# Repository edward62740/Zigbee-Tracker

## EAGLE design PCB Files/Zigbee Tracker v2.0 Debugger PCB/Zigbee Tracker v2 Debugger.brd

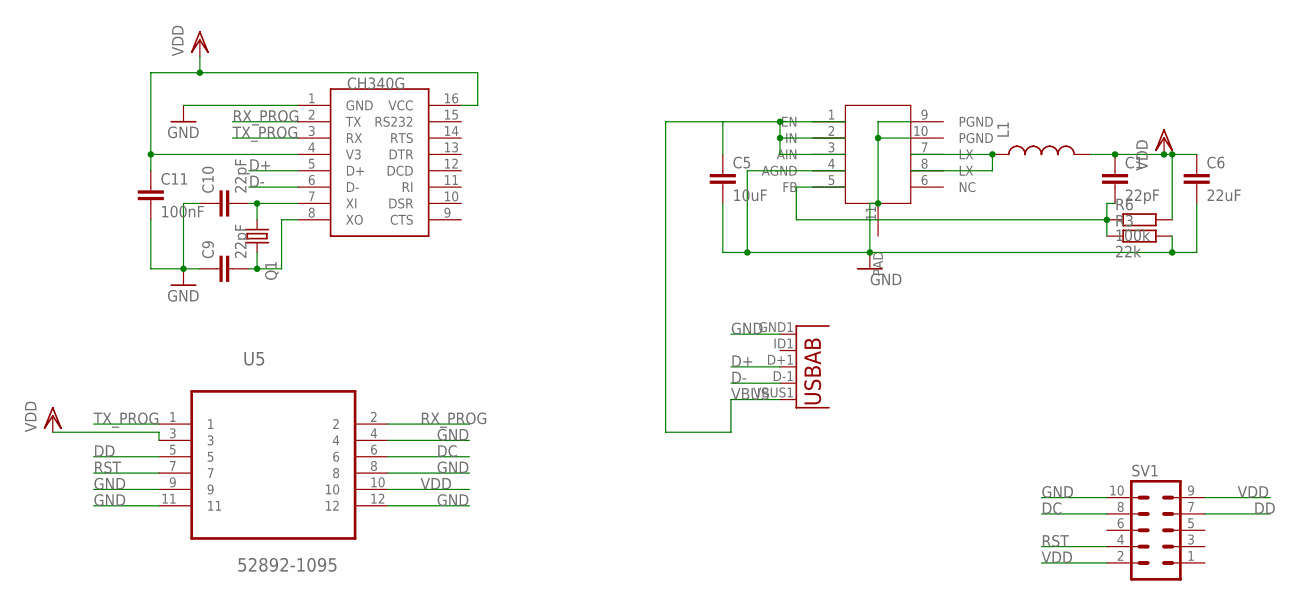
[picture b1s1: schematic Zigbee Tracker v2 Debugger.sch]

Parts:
C1, C9, C10: 22pF; C0402
C5: 10uF; C0402
C6: 22uF; C0402
C11: 100nF; C0402
L1: INDUCTOR; L0603
Q1: KX-7; 3.2X2.5_KX-7
R3: 22k; R0402
R6: 100k; R0402
SV1: MA05-2
U1: USB""; USB-MICRO-SMD
U5: 52892-1095; MOLEX_52892-1095
U$1: XM5152; SON50P300X300X80-11T170X240
U$2: CH340G; SOIC16

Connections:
D+: U1.D+1 (D+), U$2.5 (D+)
D-: U1.D-1 (D-), U$2.6 (D-)
DC: SV1.8, U5.6
DD: SV1.7, U5.5
GND: C5.2, C6.2, C9.1, C10.1, C11.2, R3.2, SV1.10, U1.GND1 (GND), U5.4, U5.8, U5.9, U5.11, U5.12, U$1.4 (AGND), U$1.9 (PGND), U$1.10 (PGND), U$1.11 (PAD), U$2.1 (GND)
unnamed: L1.1, U$1.7 (LX), U$1.8 (LX)
unnamed: C9.2, Q1.3 (2), U$2.8 (XO)
unnamed: C10.2, Q1.1, U$2.7 (XI)
unnamed: C1.2, R3.1, R6.1, U$1.5 (FB)
RST: SV1.4, U5.7
RX_PROG: U5.2, U$2.2 (TX)
TX_PROG: U5.1, U$2.3 (RX)
VBUS: C5.1, U1.VBUS1 (VBUS), U$1.1 (EN), U$1.2 (IN), U$1.3 (AIN)
VDD: C1.1, C6.1, C11.1, L1.2, R6.2, SV1.2, SV1.9, U5.3, U5.10, U$2.4 (V3), U$2.16 (VCC)

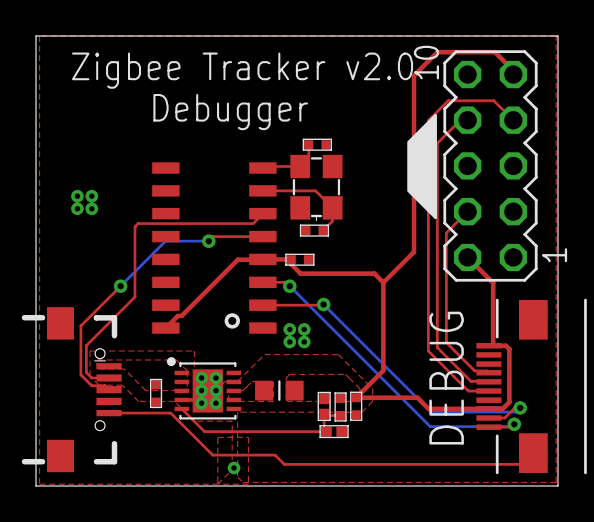
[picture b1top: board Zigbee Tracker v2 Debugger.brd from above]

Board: 2 copper layers, 29.0 x 25.0 mm, 15 parts (0 on the bottom side), 14 nets.

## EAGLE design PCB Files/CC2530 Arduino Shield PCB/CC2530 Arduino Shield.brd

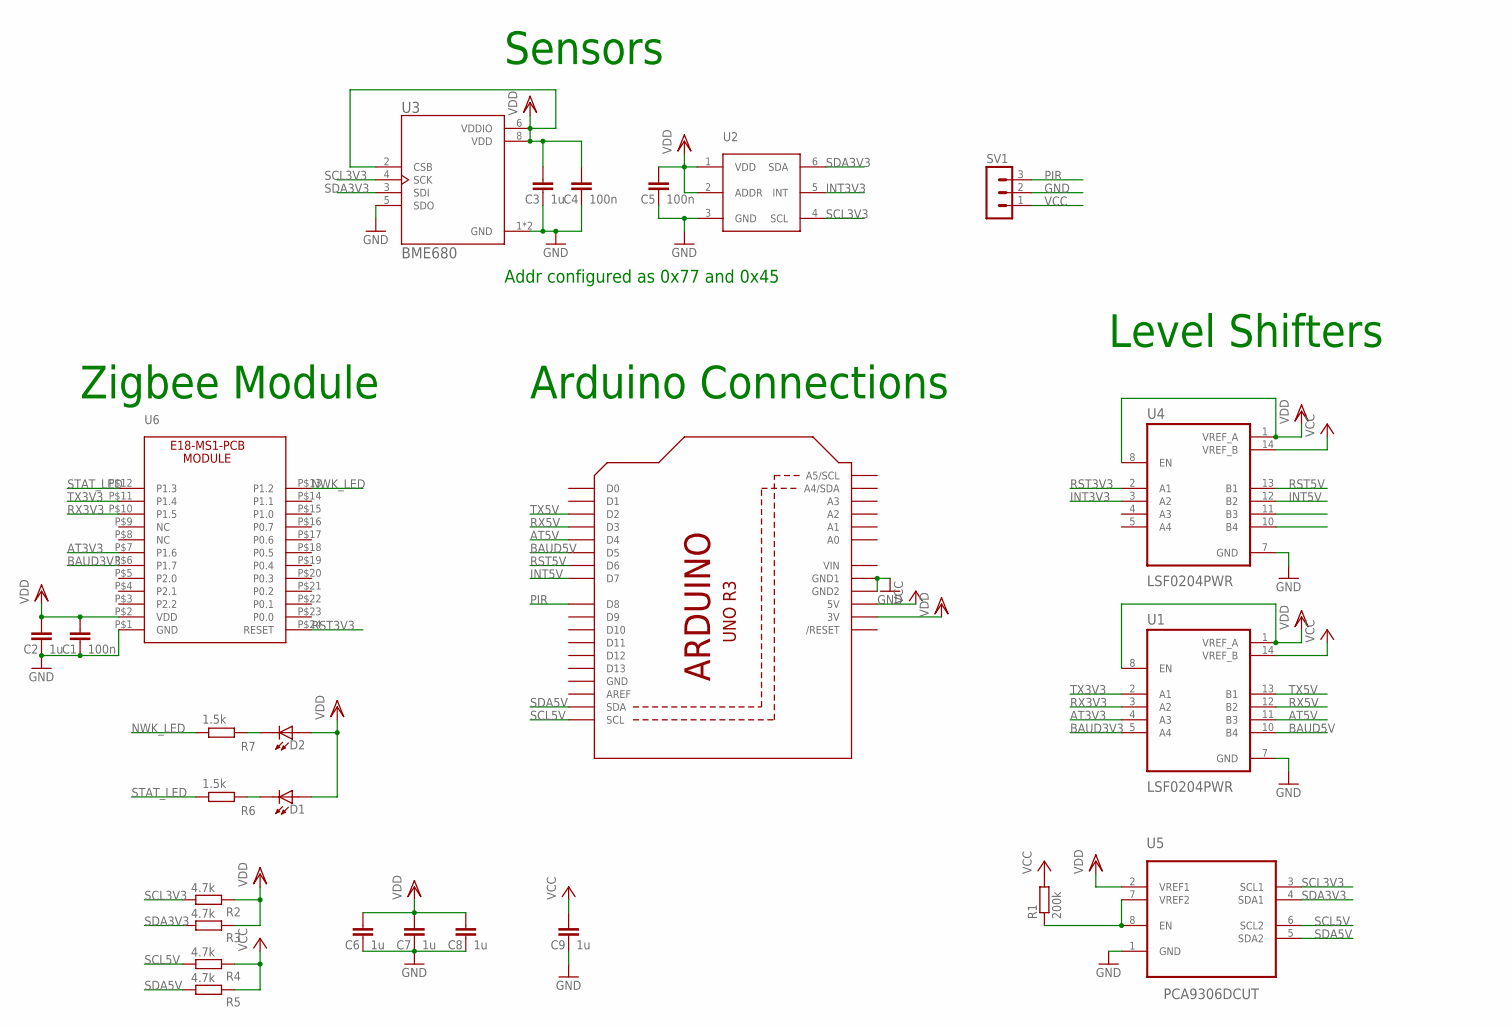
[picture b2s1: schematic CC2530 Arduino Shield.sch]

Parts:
C1, C4, C5: 100n; C0402
C2, C3, C6, C7, C8, C9: 1u; C0402
D1, D2: VLMG1500-GS08; LEDC1005X35N
Q1: ARDUINOR3-NOIOREF-NOTEXT; ARDUINOR3-NOTEXT-NOIOREF
R1: 200k; R0402
R2, R3, R4, R5: 4.7k; R0402
R6, R7: 1.5k; R0402
SV1: MA03-1
U1, U4: LSF0204PWR; SOP65P640X120-14N
U2: TI-OPT3001
U3: BME680; PSON80P300X300X100-8N
U5: PCA9306DCUT; SOP50P310X90-8N
U6: E18; E18-MS1-PCB

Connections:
AT3V3: U1.4 (A3), U6.P$7 (P1.6)
AT5V: Q1.D4, U1.11 (B3)
BAUD3V3: U1.5 (A4), U6.P$6 (P1.7)
BAUD5V: Q1.D5, U1.10 (B4)
GND: C1.2, C2.2, C3.2, C4.2, C5.2, C6.2, C7.2, C8.2, C9.2, Q1.GND, Q1.GND1, Q1.GND2, SV1.2, U1.7 (GND), U2.3 (GND), U3.1 (GND), U3.5 (SDO), U3.7 (GND), U4.7 (GND), U5.1 (GND), U6.P$1 (GND)
INT3V3: U2.5 (INT), U4.3 (A2)
INT5V: Q1.D7, U4.12 (B2)
unnamed: R1.1, U5.7 (VREF2), U5.8 (EN)
unnamed: D2.2, R7.2
unnamed: D1.2, R6.2
NWK_LED: R7.1, U6.P$13 (P1.2)
PIR: Q1.D8, SV1.3
RST3V3: U4.2 (A1), U6.P$24 (RESET)
RST5V: Q1.D6, U4.13 (B1)
RX3V3: U1.3 (A2), U6.P$10 (P1.5)
RX5V: Q1.D3, U1.12 (B2)
SCL3V3: R2.2, U2.4 (SCL), U3.4 (SCK), U5.3 (SCL1)
SCL5V: Q1.SCL, R4.2, U5.6 (SCL2)
SDA3V3: R3.2, U2.6 (SDA), U3.3 (SDI), U5.4 (SDA1)
SDA5V: Q1.SDA, R5.2, U5.5 (SDA2)
STAT_LED: R6.1, U6.P$12 (P1.3)
TX3V3: U1.2 (A1), U6.P$11 (P1.4)
TX5V: Q1.D2, U1.13 (B1)
VCC: C9.1, Q1.5V, R1.2, R4.1, R5.1, SV1.1, U1.14 (VREF_B), U4.14 (VREF_B)
VDD: C1.1, C2.1, C3.1, C4.1, C5.1, C6.1, C7.1, C8.1, D1.1, D2.1, Q1.3V, R2.1, R3.1, U1.1 (VREF_A), U1.8 (EN), U2.1 (VDD), U2.2 (ADDR), U3.2 (CSB), U3.6 (VDDIO), U3.8 (VDD), U4.1 (VREF_A), U4.8 (EN), U5.2 (VREF1), U6.P$2 (VDD)
VIN: Q1.VIN

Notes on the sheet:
Sensors
Zigbee Module
Arduino Connections
Level Shifters
Addr configured as 0x77 and 0x45

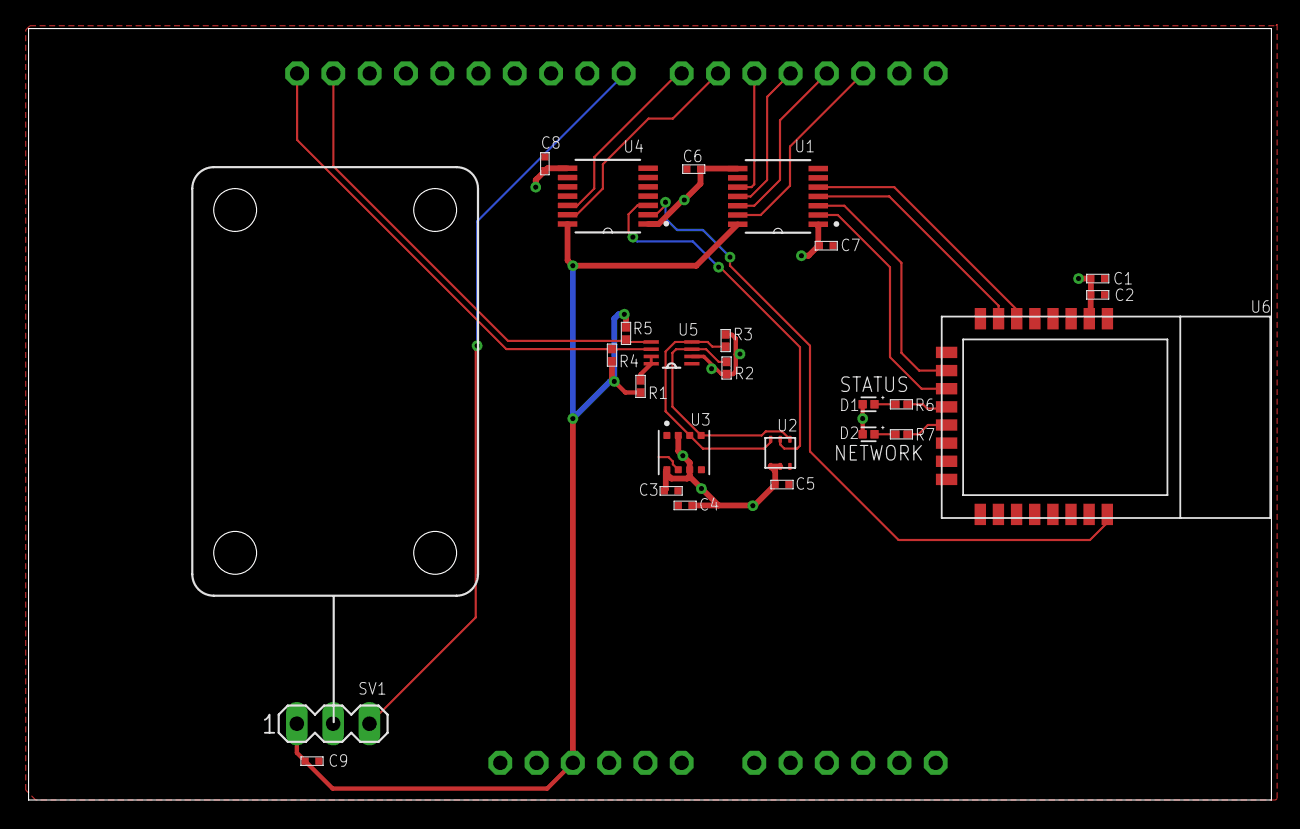
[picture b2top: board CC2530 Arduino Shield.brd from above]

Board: 2 copper layers, 87.0 x 54.0 mm, 26 parts (0 on the bottom side), 25 nets.

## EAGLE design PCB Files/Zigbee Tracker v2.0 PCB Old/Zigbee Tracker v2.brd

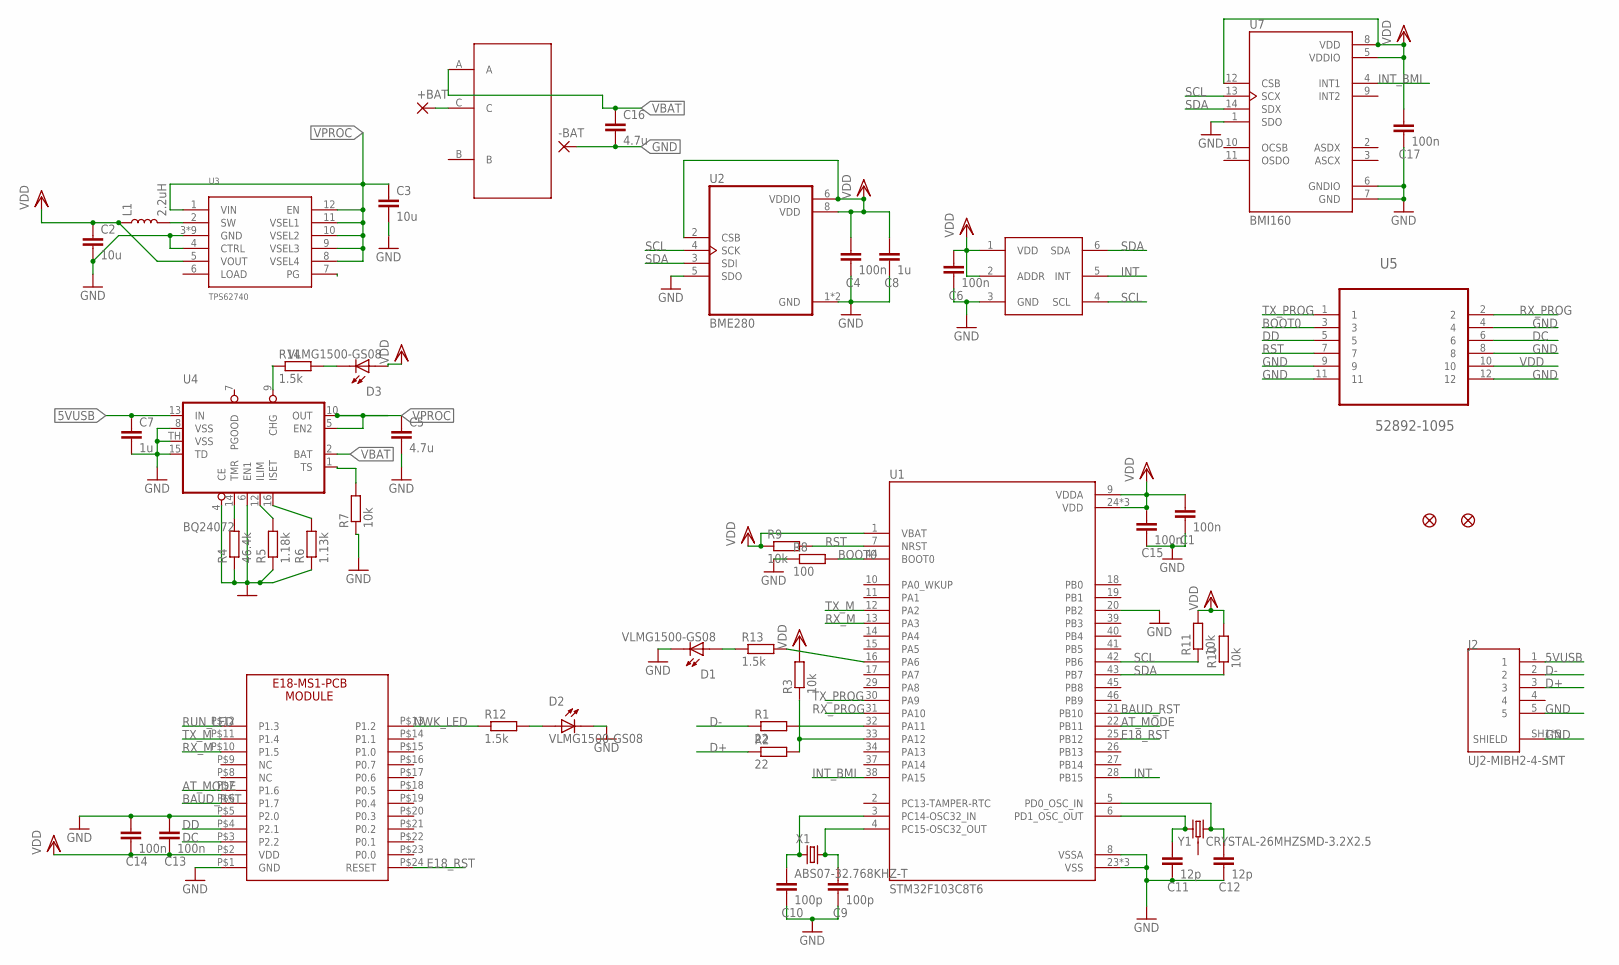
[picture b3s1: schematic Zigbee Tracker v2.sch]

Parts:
+BAT: 1,6/0,8
-BAT: 1,6/0,8
C1, C4, C6, C13, C14, C15, C17: 100n; C0402
C2, C3: 10u; C0402
C5, C16: 4.7u; C0402
C7, C8: 1u; C0402
C9, C10: 100p; C0402
C11, C12: 12p; C0402
D1, D2, D3: VLMG1500-GS08; LEDC1005X35N
FD1, FD2: FIDUCIALUFIDUCIAL; FIDUCIAL-MICRO
J2: UJ2-MIBH2-4-SMT; CUI_UJ2-MIBH2-4-SMT
L1: 2.2uH; 0805
R1, R2: 22; R0402
R3, R7, R9, R10, R11: 10k; R0402
R4: 46.4k; R0402
R5: 1.18k; R0402
R6: 1.13k; R0402
R8: 100; R0402
R12, R13, R14: 1.5k; R0402
U1: STM32F103C8T6; QFP50P900X900X160-48N
U2: BME280; PSON65P250X250X100-8N
U3: TPS62740; DSS
U4: BQ24072; S-PVQFN-N16
U5: 52892-1095; MOLEX_52892-1095
U7: BMI160; PQFN50P300X250X88-14N
U$1: E18; E18-MS1-PCB
U$2: TI-OPT3001
U$3: SMDTOGGLESWITCH
X1: ABS07-32.768KHZ-T
Y1: CRYSTAL-26MHZSMD-3.2X2.5; CRYSTAL-SMD-3.2X2.5MM

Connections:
5VUSB: C7.1, J2.1, U4.13 (IN)
AT_MODE: U1.22 (PB11), U$1.P$7 (P1.6)
BAUD_RST: U1.21 (PB10), U$1.P$6 (P1.7)
BOOT0: R8.2, U1.44 (BOOT0), U5.3
D+: J2.3, R2.1
D-: J2.2, R1.1
DC: U5.6, U$1.P$3 (P2.2)
DD: U5.5, U$1.P$4 (P2.1)
E18_RST: U1.25 (PB12), U$1.P$24 (RESET)
GND: -BAT.1, C1.2, C2.2, C3.2, C4.2, C5.2, C6.2, C7.2, C8.2, C9.2, C10.2, C11.2, C12.2, C13.1, C14.1, C15.2, C16.2, C17.2, D1.2, D2.2, J2.5, J2.SH1 (SHIELD), J2.SH2 (SHIELD), J2.SH3 (SHIELD), J2.SH4 (SHIELD), J2.SH5 (SHIELD), R4.1, R5.1, R6.1, R7.1, R8.1, U1.8 (VSSA), U1.20 (PB2), U1.23 (VSS), U1.35 (VSS), U1.47 (VSS), U2.1 (GND), U2.5 (SDO), U2.7 (GND), U3.3 (GND), U3.4 (CTRL), U3.13 (GND), U3.14 (GND), U3.15 (GND), U3.16 (GND), U3.18 (GND), U3.19 (GND), U3.20 (GND), U3.P$18 (GND), U4.4 (CE), U4.6 (EN1), U4.8 (VSS), U4.15 (TD), U4.TH (VSS), U5.4, U5.8, U5.9, U5.11, U5.12, U7.1 (SDO), U7.6 (GNDIO), U7.7 (GND), U$1.P$1 (GND), U$1.P$5 (P2.0), U$2.3 (GND)
INT: U1.28 (PB15), U$2.5 (INT)
INT_BMI: U1.38 (PA15), U7.4 (INT1)
unnamed: R1.2, U1.32 (PA11)
unnamed: R2.2, R3.1, U1.33 (PA12)
unnamed: C10.1, U1.3 (PC14-OSC32_IN), X1.1
unnamed: C9.1, U1.4 (PC15-OSC32_OUT), X1.2
unnamed: C12.1, U1.5 (PD0_OSC_IN), Y1.3 (2)
unnamed: L1.2, U3.2 (SW)
unnamed: C11.1, U1.6 (PD1_OSC_OUT), Y1.1
unnamed: R4.2, U4.14 (TMR)
unnamed: R5.2, U4.12 (ILIM)
unnamed: +BAT.1, U$3.C
unnamed: D2.1, R12.2
unnamed: R6.2, U4.16 (ISET)
unnamed: R13.2, U1.16 (PA6)
unnamed: D1.1, R13.1
unnamed: D3.2, R14.2
unnamed: R14.1, U4.9 (CHG)
NWK_LED: R12.1, U$1.P$13 (P1.2)
PG_SMR: U3.7 (PG)
RST: R9.2, U1.7 (NRST), U5.7
RUN_LED: U$1.P$12 (P1.3)
RX_M: U1.13 (PA3), U$1.P$10 (P1.5)
RX_PROG: U1.31 (PA10), U5.2
SCL: R11.1, U1.42 (PB6), U2.4 (SCK), U7.13 (SCX), U$2.4 (SCL)
SDA: R10.1, U1.43 (PB7), U2.3 (SDI), U7.14 (SDX), U$2.6 (SDA)
TS: R7.2, U4.1 (TS)
TX_M: U1.12 (PA2), U$1.P$11 (P1.4)
TX_PROG: U1.30 (PA9), U5.1
VBAT: C16.1, U4.2 (BAT), U$3.A
VDD: C1.1, C2.1, C4.1, C6.1, C8.1, C13.2, C14.2, C15.1, C17.1, D3.1, L1.1, R3.2, R9.1, R10.2, R11.2, U1.1 (VBAT), U1.9 (VDDA), U1.24 (VDD), U1.36 (VDD), U1.48 (VDD), U2.2 (CSB), U2.6 (VDDIO), U2.8 (VDD), U3.5 (VOUT), U5.10, U7.5 (VDDIO), U7.8 (VDD), U7.12 (CSB), U$1.P$2 (VDD), U$2.1 (VDD), U$2.2 (ADDR)
VPROC: C3.1, C5.1, U3.1 (VIN), U3.8 (VSEL4), U3.9 (VSEL3), U3.10 (VSEL2), U3.11 (VSEL1), U3.12 (EN), U4.5 (EN2), U4.10 (OUT)

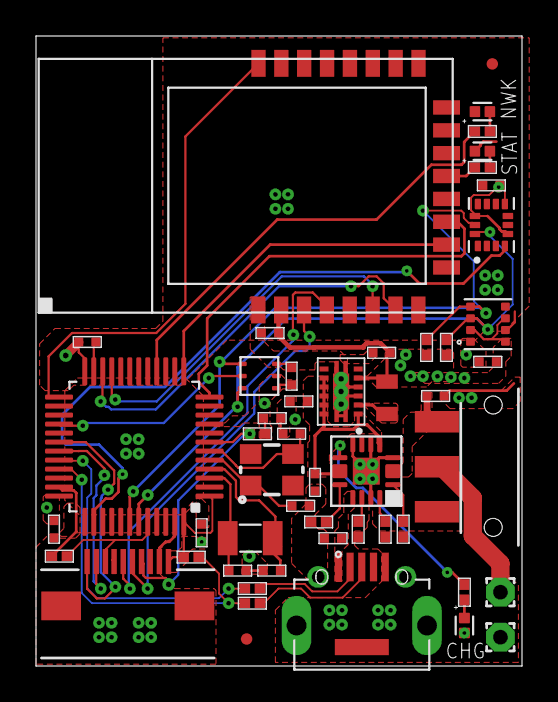
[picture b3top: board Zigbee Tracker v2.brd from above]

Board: 4 copper layers, 27.0 x 35.0 mm, 51 parts (0 on the bottom side), 40 nets.

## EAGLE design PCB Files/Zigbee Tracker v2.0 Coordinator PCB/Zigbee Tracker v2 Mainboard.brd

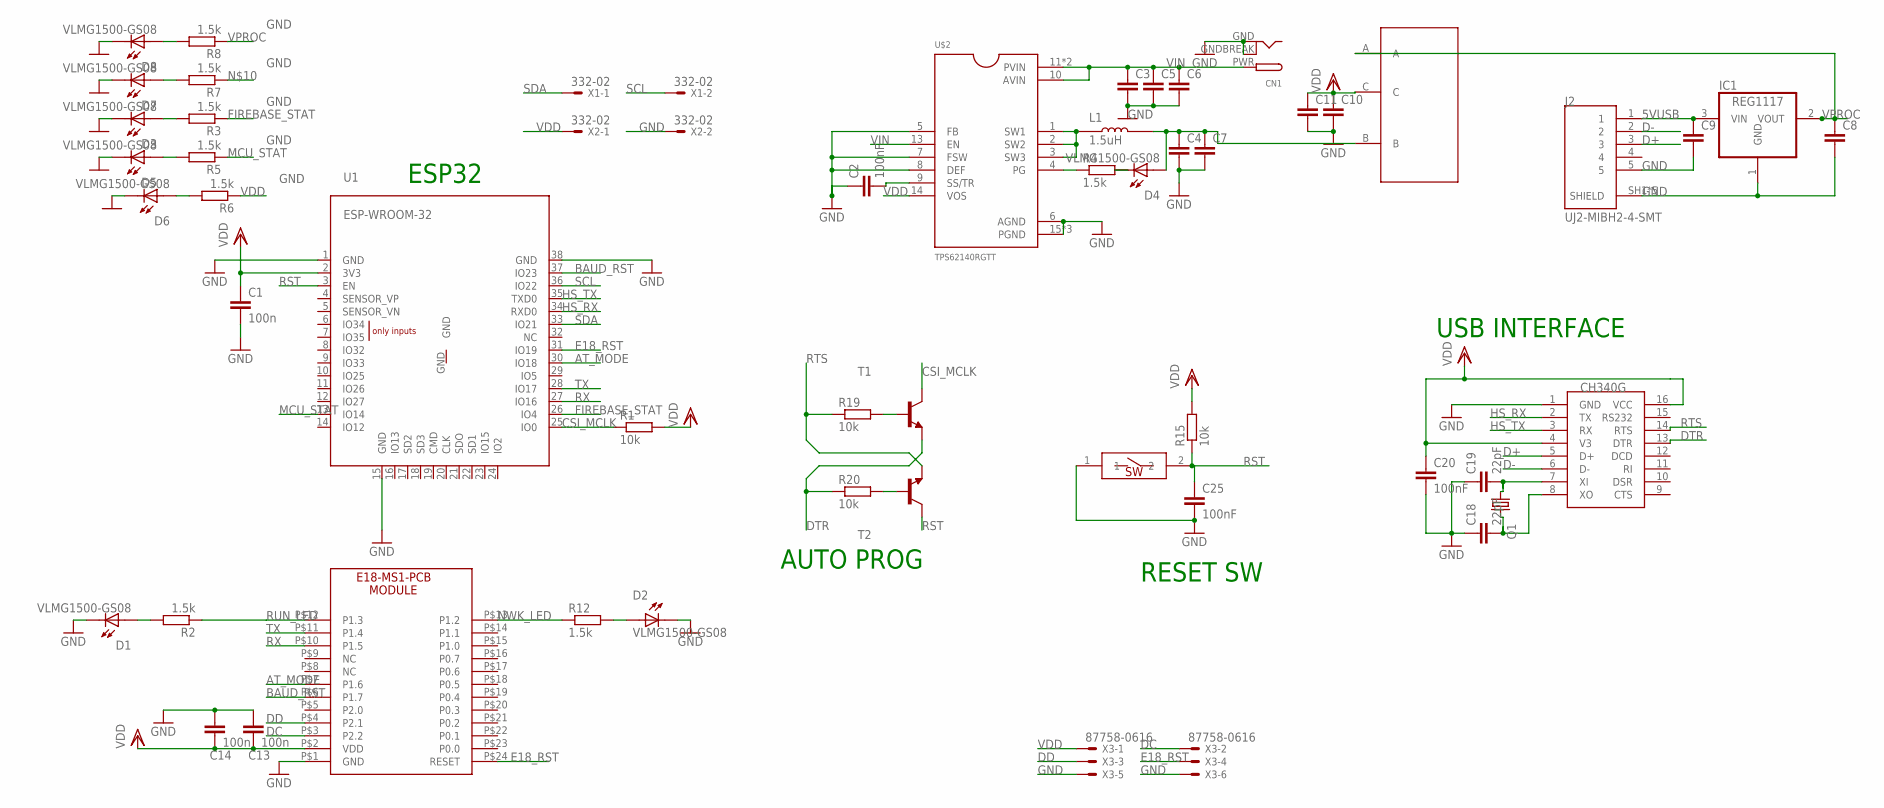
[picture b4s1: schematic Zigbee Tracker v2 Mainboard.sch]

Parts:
C1, C13, C14: 100n; C0603
C2, C25: 100nF; C0402
C3, C4: CC0402; C0402
C5, C6, C7, C10, C11: CC1210; C1210
C8, C9: CC0603; C0603
C18, C19: 22pF; C0402
C20: 100nF; C0603
CN1: DCBARRELPTH; DCJACK_2MM_PTH
D1, D2, D3, D4, D5, D6, D7, D8: VLMG1500-GS08; LEDC1005X35N
IC1: REG1117; SOT223
J2: UJ2-MIBH2-4-SMT; CUI_UJ2-MIBH2-4-SMT
L1: 1.5uH; INDC2520X120N
Q1: KX-7; 3.2X2.5_KX-7
R1, R15, R19, R20: 10k; R0402
R2, R3, R4, R5, R6, R7, R8, R12: 1.5k; R0402
RESET: SMDSWITCH; RESC4217X170
T1, T2: -NPN-SOT23-BEC; SOT23-BEC
U1: ESP-WROOM-32
U5: H; SOIC16
U$1: E18; E18-MS1-PCB
U$2: TPS62140RGTT; QFN50P300X300X100-17N
U$3: SMDTOGGLESWITCH
X1, X2: 332-02
X3: 87758-0616

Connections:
5VUSB: C9.1, IC1.3 (VIN), J2.1
AT_MODE: U1.30 (IO18), U$1.P$7 (P1.6)
BAUD_RST: U1.37 (IO23), U$1.P$6 (P1.7)
CSI_MCLK: R1.1, T1.C, U1.25 (IO0)
D+: J2.3, U5.5 (D+)
D-: J2.2, U5.6 (D-)
DC: U$1.P$3 (P2.2), X3.2
DD: U$1.P$4 (P2.1), X3.3
DTR: R20.1, T1.E, U5.13 (DTR)
E18_RST: U1.31 (IO19), U$1.P$24 (RESET), X3.4
FIREBASE_STAT: R3.1, U1.26 (IO4)
GND: C1.2, C2.1, C3.2, C4.2, C5.2, C6.2, C7.2, C8.2, C9.2, C10.2, C11.2, C13.1, C14.1, C18.1, C19.1, C20.2, C25.2, CN1.GND, CN1.GNDBREAK, D1.2, D2.2, D3.2, D5.2, D6.2, D7.2, D8.2, IC1.1 (GND), J2.5, J2.SH1 (SHIELD), J2.SH2 (SHIELD), J2.SH3 (SHIELD), J2.SH4 (SHIELD), J2.SH5 (SHIELD), RESET.1, U1.1 (GND), U1.15 (GND), U1.38 (GND), U5.1 (GND), U$1.P$1 (GND), U$2.5 (FB), U$2.6 (AGND), U$2.7 (FSW), U$2.8 (DEF), U$2.15 (PGND), U$2.16 (PGND), U$2.TH (PGND), X2.2, X3.5, X3.6
HS_RX: U1.34 (RXD0), U5.2 (TX)
HS_TX: U1.35 (TXD0), U5.3 (RX)
MCU_STAT: R5.1, U1.13 (IO14)
unnamed: L1.1, U$2.1 (SW1), U$2.2 (SW2), U$2.3 (SW3)
unnamed: C2.2, U$2.9 (SS/TR)
unnamed: R19.2, T1.B
unnamed: D1.1, R2.2
unnamed: C18.2, Q1.3 (2), U5.8 (XO)
unnamed: R20.2, T2.B
unnamed: D3.1, R3.2
unnamed: D4.2, R4.2
unnamed: C19.2, Q1.1, U5.7 (XI)
unnamed: C4.1, C7.1, D4.1, L1.2, R7.1, U$3.B
unnamed: D2.1, R12.2
unnamed: R4.1, U$2.4 (PG)
unnamed: D5.1, R5.2
unnamed: D6.1, R6.2
unnamed: D7.1, R7.2
unnamed: D8.1, R8.2
NWK_LED: R12.1, U$1.P$13 (P1.2)
RST: C25.1, R15.1, RESET.2, T2.C, U1.3 (EN)
RTS: R19.1, T2.E, U5.14 (RTS)
RUN_LED: R2.1, U$1.P$12 (P1.3)
RX: U1.27 (IO16), U$1.P$10 (P1.5)
SCL: U1.36 (IO22), X1.2
SDA: U1.33 (IO21), X1.1
TX: U1.28 (IO17), U$1.P$11 (P1.4)
VDD: C1.1, C10.1, C11.1, C13.2, C14.2, C20.1, R1.2, R6.1, R15.2, U1.2 (3V3), U5.4 (V3), U5.16 (VCC), U$1.P$2 (VDD), U$2.14 (VOS), U$3.C, X2.1, X3.1
VIN: C3.1, C5.1, C6.1, CN1.PWR, U$2.10 (AVIN), U$2.11 (PVIN), U$2.12 (PVIN), U$2.13 (EN)
VPROC: C8.1, IC1.2 (VOUT), R8.1, U$3.A

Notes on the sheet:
RESET SW
AUTO PROG
ESP32
USB INTERFACE

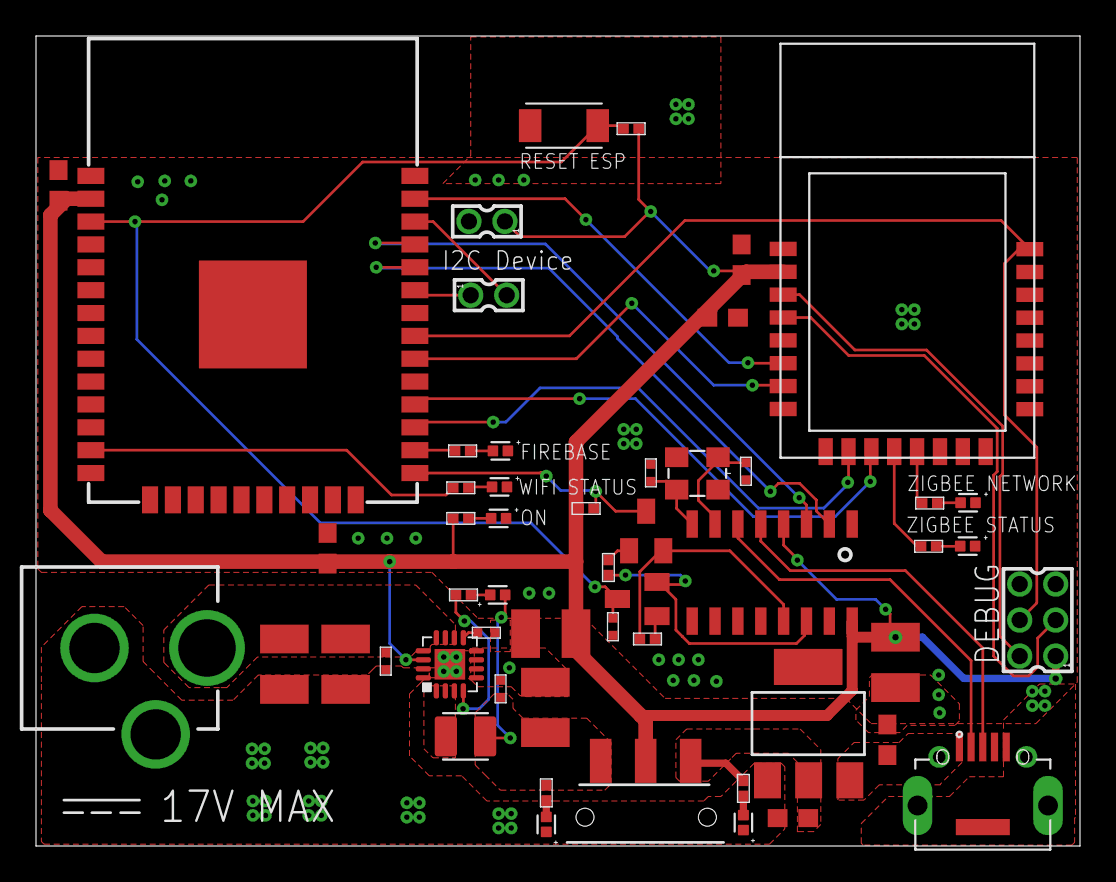
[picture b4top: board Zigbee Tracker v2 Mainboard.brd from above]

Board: 2 copper layers, 58.0 x 45.0 mm, 53 parts (0 on the bottom side), 42 nets.

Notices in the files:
parts and their libraries:
FaBo-Mems: Released under the Creative Commons Attribution-ShareAlike 4.0 License
https://creativecommons.org/licenses/by-sa/4.0
crystal-geyer_V1_0: Copyright: Geyer-Electronic
SparkFun-Coils: Licensing: Creative Commons ShareAlike 4.0 International - https://creativecommons.org/licenses/by-sa/4.0
